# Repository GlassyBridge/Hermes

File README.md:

> ⚠️ **WARNING**  
> This project has **not been tested on real hardware yet**.  
> The PCB has been designed, and the firmware is complete, but it hasn't been uploaded or verified on a physical board yet.  

# LuminanceMeter
A simple hardware project that features an Ambient Light Sensor and 0.96" OLED screen controlled by a XIAO-RP2040 microcontroller to measure light level and display it interms of lux (luminance).

## Features

- **Uses Sensor to read luminance**
- **OLED Display (128x64):** displays ambient light level in lux.  
- **Portable:** With a CR2032 battery holder you can take it anywhere after flashing it with the firmware . (You hold the button to measure luminance if you are using battery to power it.)
---
## Screenshots

### Schematic

### PCB

### 3D Front View

### 3D Back View

---

## Firmware

The firmware has been written with Arduino IDE using C++.

**Libraries used:**
- `Wire.h`: I2C communication
- `Adafruit_GFX.h`: OLED graphics
- `Adafruit_SSD1306.h`: OLED driver

---

## PCB Design

The PCB is designed using KiCad.
- All symbols are from KiCad or open-source, you can find the custom ones in the "Resources" folder.
---

## Acknowledgement
Made for [Hermes](https://hermes.hackclub.com/).
Thanks to [Meghana Madiraju](https://github.com/MeghanaM4) for hosting this event and for the support.

## License

#### [MIT License](LICENSE.txt).  
---

## Author
[GlassyBridge](https://github.com/GlassyBridge)

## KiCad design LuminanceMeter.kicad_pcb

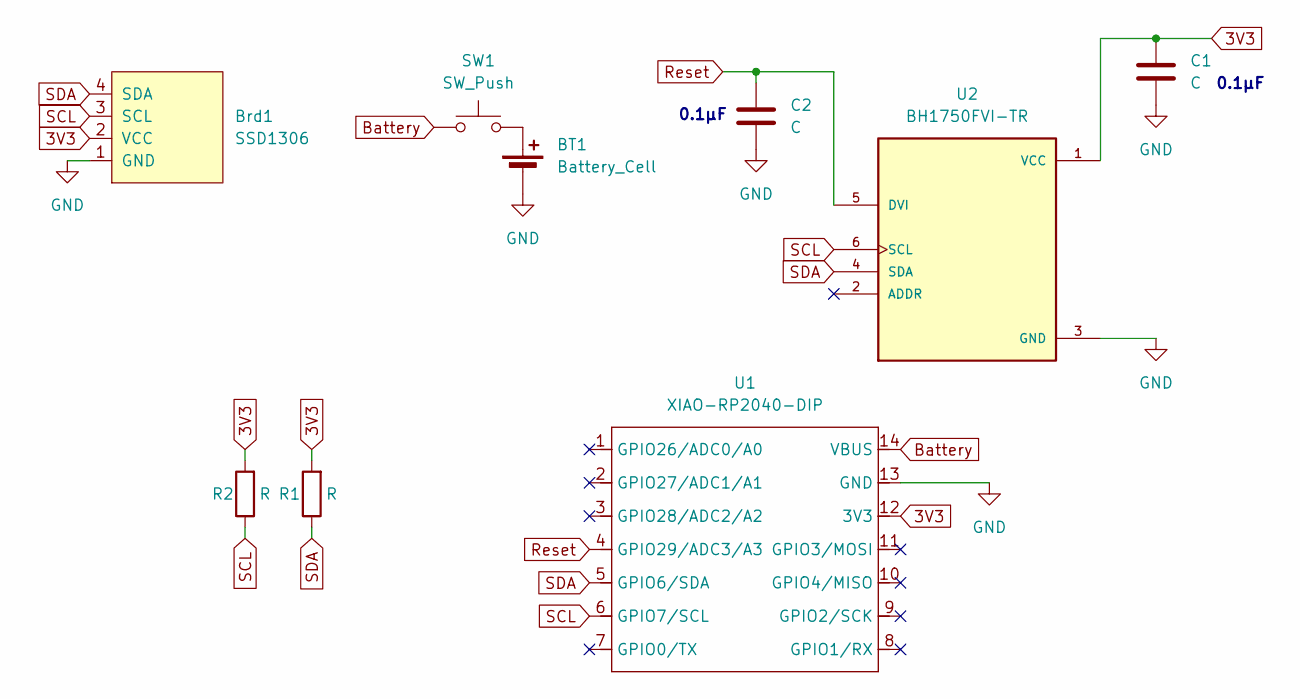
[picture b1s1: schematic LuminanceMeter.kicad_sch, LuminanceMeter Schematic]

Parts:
BT1: Battery_Cell; BatteryHolder_Keystone_3034_1x20mm
Brd1: SSD1306; 128x64OLED
C1, C2: C; CAPC1005X55N
R1, R2: R; R_Axial_DIN0204_L3.6mm_D1.6mm_P5.08mm_Horizontal
SW1: SW_Push; SW_PUSH_6mm
U1: XIAO-RP2040-DIP
U2: BH1750FVI-TR; XDCR_BH1750FVI-TR; PARTREV D

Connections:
3V3: Brd1.2 (VCC), C1.1, R1.2, R2.2, U1.12 (3V3), U2.1 (VCC)
Battery: SW1.1, U1.14 (VBUS)
GND: BT1.2 (-), Brd1.1 (GND), C1.2, C2.2, U1.13 (GND), U2.3 (GND)
unnamed: BT1.1 (+), SW1.2
Reset: C2.1, U1.4 (GPIO29/ADC3/A3), U2.5 (DVI)
SCL: Brd1.3 (SCL), R2.1, U1.6 (GPIO7/SCL), U2.6 (SCL)
SDA: Brd1.4 (SDA), R1.1, U1.5 (GPIO6/SDA), U2.4 (SDA)

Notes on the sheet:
0.1µF

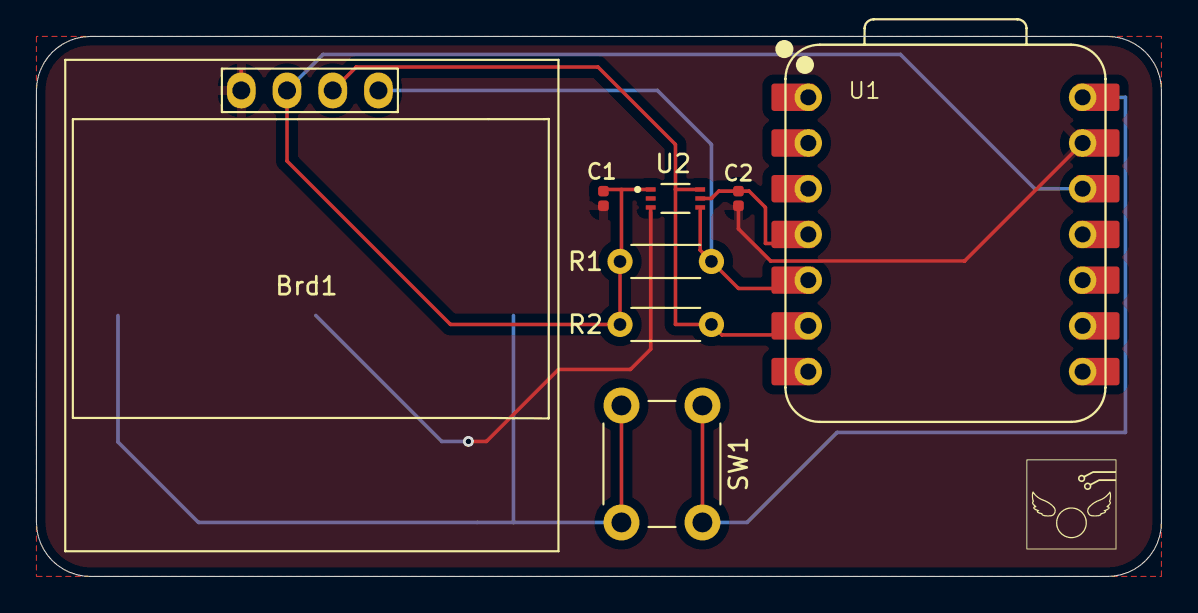
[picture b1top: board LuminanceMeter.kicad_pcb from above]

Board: 2 copper layers, 62.5 x 30.0 mm, 9 parts (1 on the bottom side), 7 nets.

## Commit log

2025-08-02 init
2025-08-07 Fix Images not loading
